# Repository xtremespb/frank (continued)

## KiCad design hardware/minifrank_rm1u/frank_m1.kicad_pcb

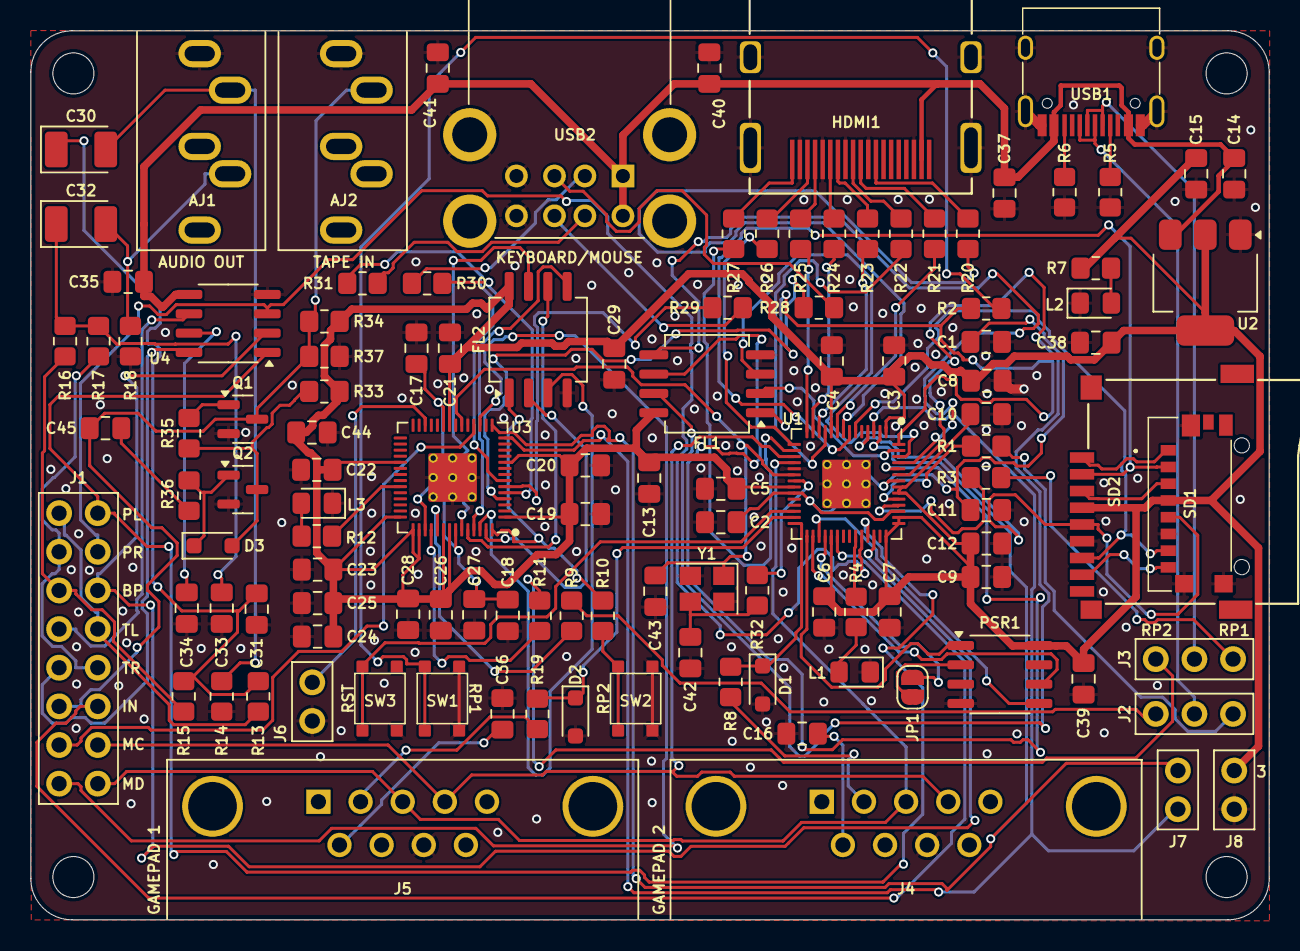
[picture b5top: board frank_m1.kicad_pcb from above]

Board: 2 copper layers, 81.4 x 58.4 mm, 121 parts (0 on the bottom side), 107 nets.

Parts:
AJ1, AJ2: SJ1-353XNG; Jack (3.5mm)
C1, C2, C3, C4, C5, C6, C7, C8, C9, C10, C13, C16, C17, C18, C19, C20, C21, C22, C23, C24, C25, C26, C29, C36, C37, C38, C39, C44, C45: 100n; Capacitor (0805)
C11, C12, C27, C28, C34: 1u; Capacitor (0805)
C14, C15, C40, C41: 10u; Capacitor (0805)
C30, C32: 10u; Capacitor (3528, tantalum, polar)
C31, C33: 10n; Capacitor (0805)
C35: 47u; Capacitor (0805)
C42, C43: 15p; Capacitor (0805)
D1, D2: 3V3; Diode (SOD-323)
D3: 1N4148; Diode (SOD-323)
FL1, FL2: W25Q128JVSIQ; SOIC-8
H1, H2, H3, H4: MountingHole; MountingHole_2.7mm
HDMI1: DC3RX19JA2; HDMI (female)
J1: Main Jumpers; Pin Header (2x08)
J2: USB DP Jumper; Pin Header (1x03)
J3: USB DM Jumper; Pin Header (1x03)
J4, J5: Gamepad; D-SUB (9 pin, male, top mount)
J6: RP2 Reset; Pin Header (1x02)
J7: UART; Pin Header (1x02)
J8: +3.3V; Pin Header (1x02)
JP1: Jumper PSRAM (2.54); Jumper (solder)
L1, L3: Blue; LED (0805)
L2: Green; LED (0805)
PSR1: ESP-PSRAM32; SO-8
Q1, Q2: BC850; SOT-23
R1, R3, R9, R11: 27R; Resistor (0805)
R2, R4, R7, R8, R10, R12, R13, R17, R19, R32, R34: 1K; Resistor (0805)
R5, R6: 5.1K; Resistor (0805)
R14, R18: 330R; Resistor (0805)
R15, R16: 2K; Resistor (0805)
R20, R21, R22, R23, R24, R25, R26, R27: 270R; Resistor (0805)
R28, R29, R30, R31: 22R; Resistor (0805)
R33, R35, R36: 10K; Resistor (0805)
R37: 100R; Resistor (0805)
SD1: 47571-0001; MicroSD (SMD, short)
SD2: 104031-0811; MicroSD (SMD, long)
SW1, SW2: KLS7-TS3302; Button (SMD, 3x3mm, 1-1)
SW3: KLS7-TS3302; Button (SMD, 3x3mm)
U1, U3: RP2040; QFN 56
U2: NCP1117 3.3; SOT-223
U4: TDA1387T; SO-8
USB1: USB4215; USB Type C
USB2: SS-52100-004; USB Type A (stacked)
Y1: 12 MHz; Crystal (3225)

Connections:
+3V3: C3.1, C4.1, C5.1, C6.1, C7.1, C8.1, C9.1, C10.1, C12.1, C13.1, C15.1, C19.1, C20.1, C21.1, C22.1, C23.1, C24.1, C25.1, C26.1, C28.1, C29.1, C38.2, C39.1, C44.1, FL1.8 (VCC), FL2.8 (VCC), J8.1, PSR1.8 (VCC), R7.2, R33.1, R34.1, SD1.P4 (VDD), SD2.4 (VDD), U1.1 (IOVDD), U1.10 (IOVDD), U1.22 (IOVDD), U1.33 (IOVDD), U1.42 (IOVDD), U1.43 (ADC_AVDD), U1.44 (VREG_IN), U1.48 (USB_VDD), U1.49 (IOVDD), U2.2 (VO), U3.1 (IOVDD), U3.10 (IOVDD), U3.22 (IOVDD), U3.33 (IOVDD), U3.42 (IOVDD), U3.43 (ADC_AVDD), U3.44 (VREG_IN), U3.48 (USB_VDD), U3.49 (IOVDD)
/A_OUTB: J1.5, R15.2, R16.2
/A_OUTL: J1.1, J1.8, R13.2
/A_OUTR: J1.3, J1.10, R17.2
/A_TDAL: J1.7, U4.6 (A_LEFT)
/A_TDAR: J1.9, U4.8 (A_RIGHT)
/Audio Out/L: AJ1.T, C30.2, R14.1
/Audio Out/R: AJ1.R, C32.2, R18.1
/GPIO0: J7.1, U1.2 (GPIO0), U3.15 (GPIO12)
/GPIO1: J7.2, U1.3 (GPIO1), U3.14 (GPIO11)
/GPIO2: SD1.P5 (CLK), SD2.5 (CLK), U1.4 (GPIO2)
/GPIO3: SD1.P3 (CMD), SD2.3 (CMD)
/GPIO4: SD1.P7 (DAT0), SD2.7 (DAT0), U1.6 (GPIO4)
/GPIO5: SD1.P2 (CD/DAT3), SD2.2 (DAT3/CD), U1.7 (GPIO5)
/GPIO6: R20.2, U1.8 (GPIO6)
/GPIO7: R21.2, U1.9 (GPIO7)
/GPIO8: R22.2, U1.11 (GPIO8)
/GPIO9: R23.2, U1.12 (GPIO9)
/GPIO10: R24.2, U1.13 (GPIO10)
/GPIO11: R25.2, U1.14 (GPIO11)
/GPIO12: R26.2, U1.15 (GPIO12)
/GPIO13: R27.2, U1.16 (GPIO13)
/GPIO14: J1.14, J4.4, J5.4, U1.17 (GPIO14)
/GPIO15: J1.16, J4.3, J5.3, U1.18 (GPIO15)
/GPIO16: D2.1 (K), R19.1, U1.27 (GPIO16)
/GPIO17: D1.1 (K), R8.1, U1.28 (GPIO17)
/GPIO18: PSR1.1 (~CE), U1.29 (GPIO18)
/GPIO19: PSR1.6 (SCLK), U1.30 (GPIO19)
/GPIO20: PSR1.5 (SI/SIO), U1.31 (GPIO20)
/GPIO21: JP1.2 (B), U1.32 (GPIO21)
/GPIO22: J1.12, U1.34 (GPIO22)
/GPIO26: J1.4, U1.38 (GPIO26_ADC0), U4.3 (DATA)
/GPIO27: J1.2, U1.39 (GPIO27_ADC1), U4.1 (SCLK)
/GPIO28: J1.6, U1.40 (GPIO28_ADC2), U4.2 (LRCK)
/Gamepad 1/+5V: C36.1, J5.6
/Gamepad 1/J1_DATA: J5.2, R19.2
/Gamepad 2/+5V: C16.1, J4.6
/Gamepad 2/J1_DATA: J4.2, R8.2
/LOAD_IN: AJ2.T, C45.1, J1.11, Q1.3 (C), R34.2, R37.1
/MS_CLK: J1.13, U3.18 (GPIO15)
/MS_DATA: J1.15, U3.17 (GPIO14)
/Micro SD/DAT1: SD1.P8 (DAT1), SD2.8 (DAT1)
/Micro SD/DAT2: SD1.P1 (DAT2), SD2.1 (DAT2)
/P_DM: J3.2, USB1.5 (DN2), USB1.7 (DN1)
/P_DP: J2.2, USB1.6 (DP1), USB1.8 (DP2)
/RP1/GPIO25: R4.2, U1.37 (GPIO25)
/RP1/QSPI_SCLK: FL1.6 (CLK), U1.52 (QSPI_SCLK)
/RP1/QSPI_SD0: FL1.5 (DI(IO0)), U1.53 (QSPI_SD0)
/RP1/QSPI_SD1: FL1.2 (DO(IO1)), U1.55 (QSPI_SD1)
/RP1/QSPI_SD2: FL1.3 (IO2), U1.54 (QSPI_SD2)
/RP1/QSPI_SD3: FL1.7 (IO3), U1.51 (QSPI_SD3)
/RP1/QSPI_SS: FL1.1 (~CS), R2.1, U1.56 (QSPI_SS)
/RP1/~USB_BOOT: R2.2, SW1.2
/RP1_DM: J3.1, R3.1
/RP1_DP: J2.1, R1.1
/RP2/GPIO25: R12.2, U3.37 (GPIO25)
/RP2/QSPI_SCLK: FL2.6 (CLK), U3.52 (QSPI_SCLK)
/RP2/QSPI_SD0: FL2.5 (DI(IO0)), U3.53 (QSPI_SD0)
/RP2/QSPI_SD1: FL2.2 (DO(IO1)), U3.55 (QSPI_SD1)
/RP2/QSPI_SD2: FL2.3 (IO2), U3.54 (QSPI_SD2)
/RP2/QSPI_SD3: FL2.7 (IO3), U3.51 (QSPI_SD3)
/RP2/QSPI_SS: FL2.1 (~CS), R10.1, U3.56 (QSPI_SS)
/RP2/~USB_BOOT: R10.2, SW2.2
/RP2_DM: J3.3, R11.1
/RP2_DP: J2.3, R9.1
/RP2_RUN: J6.1, U3.26 (RUN)
/RUN: SW3.3, SW3.4, U1.26 (RUN)
/US_D1M: R30.1, U3.5 (GPIO3)
/US_D1P: R28.1, U3.4 (GPIO2)
/US_D2M: R31.1, U3.7 (GPIO5)
/US_D2P: R29.1, U3.6 (GPIO4)
/XIN: C43.1, U1.20 (XIN), U3.20 (XIN), Y1.1
/XOUT: R32.1, U1.21 (XOUT)
GND: AJ1.S, AJ2.S, C1.2, C2.2, C3.2, C4.2, C5.2, C6.2, C7.2, C8.2, C9.2, C10.2, C11.2, C12.2, C13.2, C14.2, C15.2, C16.2, C17.2, C18.2, C19.2, C20.2, C21.2, C22.2, C23.2, C24.2, C25.2, C26.2, C27.2, C28.2, C29.2, C31.2, C33.2, C34.2, C35.1, C36.2, C37.2, C38.1, C39.2, C40.2, C41.2, C42.2, C43.2, C44.2, D1.2 (A), D2.2 (A), FL1.4 (GND), FL2.4 (GND), HDMI1.2 (G_D2), HDMI1.5 (G_D1), HDMI1.8 (G_D0), HDMI1.11 (G_CLK), HDMI1.17 (G_DDC/CEC), HDMI1.20 (SHIELD1), HDMI1.21 (SHIELD2), HDMI1.22 (SHIELD3), HDMI1.23 (SHIELD4), J4.8, J5.8, J6.2, J8.2, L1.1 (K), L2.1 (K), L3.1 (K), PSR1.4 (VSS), Q1.2 (E), Q2.2 (E), R5.1, R6.1, R14.2, R18.2, R37.2, SD1.G1 (GND_1), SD1.G2 (GND_2), SD1.G3 (GND_3), SD1.P6 (VSS), SD2.6 (VSS), SW1.1, SW2.1, SW3.1, SW3.2, U1.19 (TESTEN), U1.57 (GND), U2.1 (GND), U3.19 (TESTEN), U3.57 (GND), U4.4 (AGND), USB1.1 (GND), USB1.12 (GND), USB1.13 (SHIELD), USB2.4 (GND1), USB2.8 (GND2), USB2.9 (Shield), Y1.2, Y1.4
unnamed: C30.1, C31.1, R13.1, R15.1
unnamed: C32.1, C33.1, R16.1, R17.1
unnamed: C42.1, R32.2, Y1.3
unnamed: C45.2, R36.1
unnamed: D3.2 (A), Q2.3 (C), R33.2, R35.1
unnamed: D3.1 (K), Q2.1 (B), R36.2
unnamed: HDMI1.12 (CLKN), R20.1
unnamed: HDMI1.10 (CLKP), R21.1
unnamed: HDMI1.9 (D0N), R22.1
unnamed: HDMI1.7 (D0P), R23.1
unnamed: HDMI1.6 (D1N), R24.1
unnamed: HDMI1.4 (D1P), R25.1
unnamed: HDMI1.3 (D2N), R26.1
unnamed: HDMI1.1 (D2P), R27.1
unnamed: JP1.1 (A), PSR1.2 (SO/SIO)
unnamed: L1.2 (A), R4.1
unnamed: L2.2 (A), R7.1
unnamed: L3.2 (A), R12.1
unnamed: Q1.1 (B), R35.2
unnamed: R3.2, U1.46 (USB_DM)
unnamed: R1.2, U1.47 (USB_DP)
unnamed: C1.1, C2.1, C11.1, U1.23 (DVDD), U1.45 (VREG_VOUT), U1.50 (DVDD)
unnamed: R11.2, U3.46 (USB_DM)
unnamed: R9.2, U3.47 (USB_DP)
unnamed: C17.1, C18.1, C27.1, U3.23 (DVDD), U3.45 (VREG_VOUT), U3.50 (DVDD)
unnamed: C34.1, U4.7 (FLT)
unnamed: R5.2, USB1.4 (CC1)
unnamed: R6.2, USB1.10 (CC2)
unnamed: R28.2, USB2.3 (D1+)
unnamed: R30.2, USB2.2 (D1-)
unnamed: R29.2, USB2.7 (D2+)
unnamed: R31.2, USB2.6 (D2-)
VBUS: C14.1, C35.2, C37.1, C40.1, C41.1, HDMI1.18 (+5V), U2.3 (VI), U4.5 (VA), USB1.2 (VBUS), USB1.11 (VBUS), USB2.1 (VBUS1), USB2.5 (VBUS2)

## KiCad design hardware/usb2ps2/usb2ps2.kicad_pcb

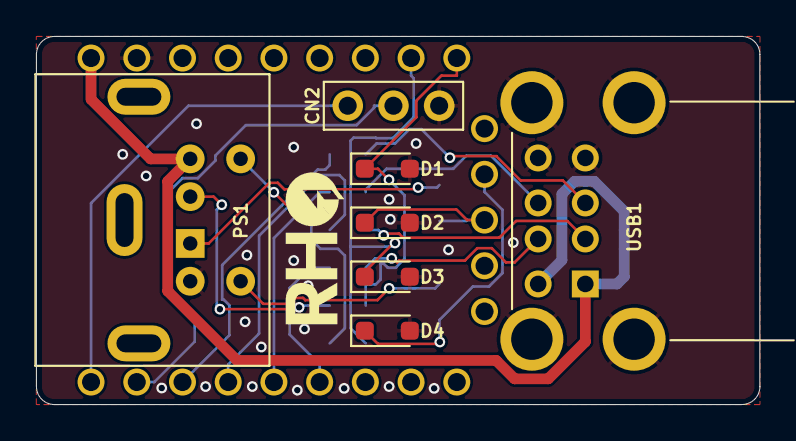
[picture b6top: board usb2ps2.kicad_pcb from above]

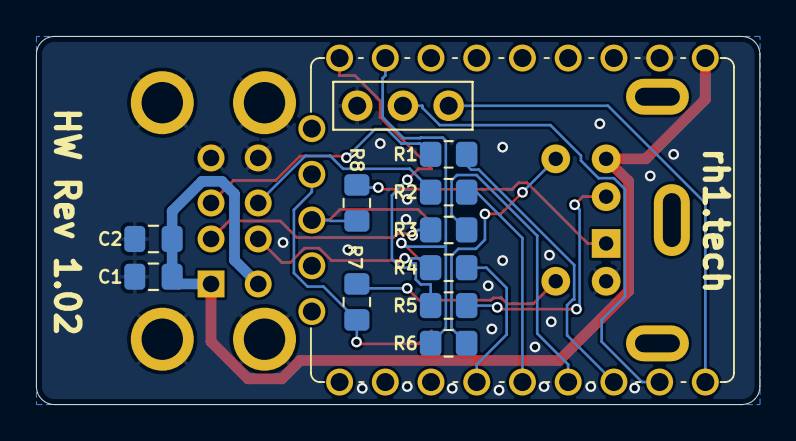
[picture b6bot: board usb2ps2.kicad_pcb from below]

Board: 2 copper layers, 40.2 x 20.4 mm, 18 parts (11 on the bottom side), 20 nets.

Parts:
C1, C2: 10u; Capacitor (0805)
CN2: UART; Pin Header (1x03)
D1, D2, D3, D4: 3V3; Diode (SOD-323)
PS1: PS/2; MiniDIN (6 Pin, female)
R1, R2, R3, R4: 22R; Resistor (0805)
R5, R6, R7, R8: 100R; Resistor (0805)
RP1: RP 2040 Zero; Raspberry Pi Zero (Outer pins)
USB1: USB_A_Stacked; USB Type A (stacked)

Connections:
/GPIO0: CN2.1, RP1.1 (0)
/GPIO1: CN2.2, RP1.2 (1)
/GPIO2: R1.1, RP1.3 (2)
/GPIO3: R3.1, RP1.4 (3)
/GPIO4: R2.1, RP1.5 (4)
/GPIO5: R4.1, RP1.6 (5)
/GPIO11: D2.1 (K), R8.2, RP1.12 (11)
/GPIO12: D4.1 (K), R7.2, RP1.13 (12)
/GPIO14: D1.1 (K), R5.2, RP1.15 (14)
/GPIO15: D3.1 (K), R6.2, RP1.16 (15)
/PS2 with Diodes/KB_CLK: PS1.5, R7.1
/PS2 with Diodes/KB_DATA: PS1.1, R8.1
/PS2 with Diodes/MS_CLK: PS1.6, R6.1
/PS2 with Diodes/MS_DATA: PS1.2, R5.1
GND: C1.2, C2.2, CN2.3, D1.2 (A), D2.2 (A), D3.2 (A), D4.2 (A), PS1.3, RP1.22 (GND), USB1.4 (GND1), USB1.8 (GND2), USB1.9 (Shield)
unnamed: R1.2, USB1.3 (D1+)
unnamed: R3.2, USB1.2 (D1-)
unnamed: R2.2, USB1.7 (D2+)
unnamed: R4.2, USB1.6 (D2-)
VBUS: C1.1, C2.1, PS1.4, RP1.23 (5V), USB1.1 (VBUS1), USB1.5 (VBUS2)

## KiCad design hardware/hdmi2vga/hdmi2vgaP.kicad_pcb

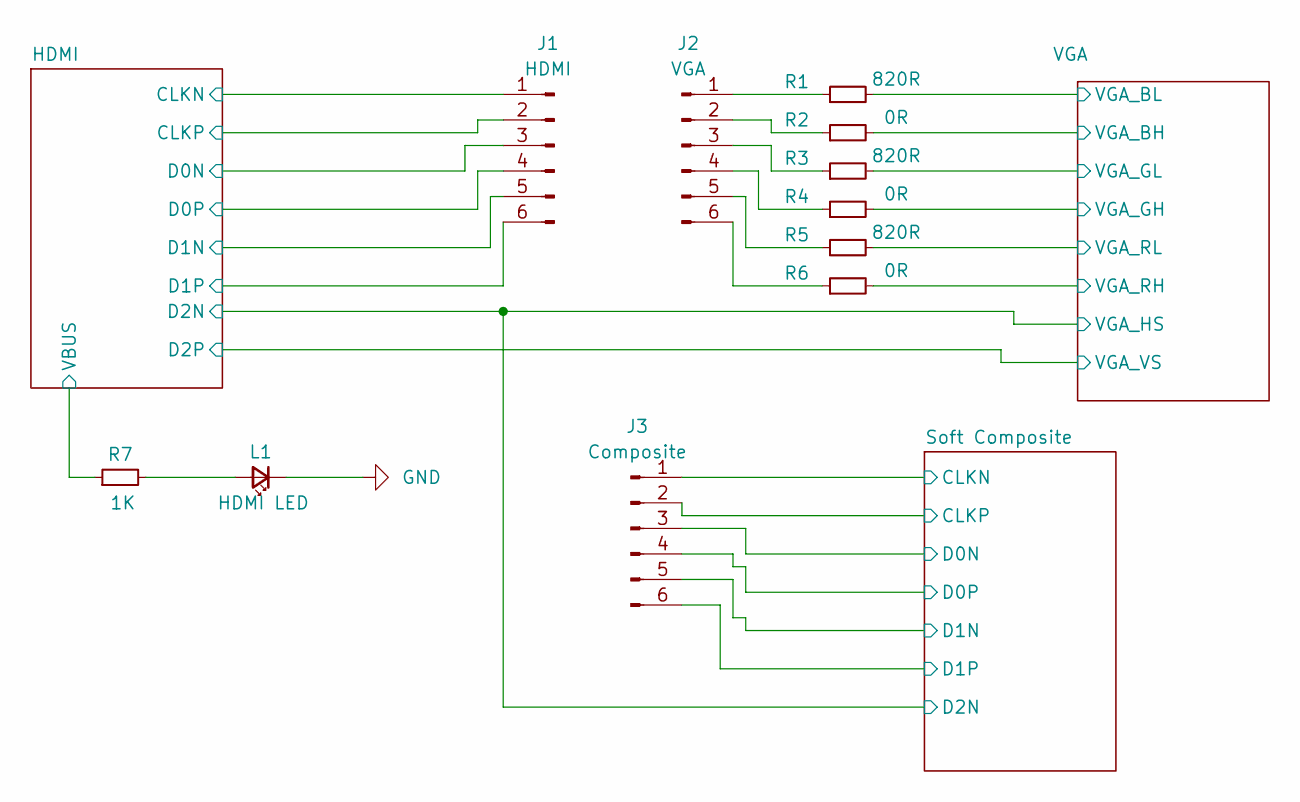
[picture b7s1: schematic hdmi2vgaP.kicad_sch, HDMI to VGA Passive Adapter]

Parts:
J1: HDMI; Medved_Pinheader_6P
J2: VGA; Medved_Pinheader_6P
J3: Composite; Medved_Pinheader_6P
L1: HDMI LED; LED_0805_2012Metric_Pad1.15x1.40mm_HandSolder
R1, R3, R5: 820R; R_0805_2012Metric_Pad1.20x1.40mm_HandSolder
R2, R4, R6: 0R; R_0805_2012Metric_Pad1.20x1.40mm_HandSolder
R7: 1K; R_0805_2012Metric_Pad1.20x1.40mm_HandSolder

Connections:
/HDMI/CLKN: J1.1; also elsewhere on the board
/HDMI/CLKP: J1.2; also elsewhere on the board
/HDMI/D0N: J1.3; also elsewhere on the board
/HDMI/D0P: J1.4; also elsewhere on the board
/HDMI/D1N: J1.5; also elsewhere on the board
/HDMI/D1P: J1.6; also elsewhere on the board
/HDMI/VBUS: R7.1; also elsewhere on the board
/Soft Composite/CLKN: J3.1; also elsewhere on the board
/Soft Composite/CLKP: J3.2; also elsewhere on the board
/Soft Composite/D0N: J3.3; also elsewhere on the board
/Soft Composite/D0P: J3.4; also elsewhere on the board
/Soft Composite/D1N: J3.5; also elsewhere on the board
/Soft Composite/D1P: J3.6; also elsewhere on the board
/VGA/VGA_BH: R1.2, R2.2; also elsewhere on the board
/VGA/VGA_GH: R3.2, R4.2; also elsewhere on the board
/VGA/VGA_RH: R5.2, R6.2; also elsewhere on the board
GND: L1.1 (K); also elsewhere on the board
unnamed: J2.1, R1.1
unnamed: J2.2, R2.1
unnamed: J2.3, R3.1
unnamed: J2.4, R4.1
unnamed: J2.5, R5.1
unnamed: J2.6, R6.1
unnamed: L1.2 (A), R7.2

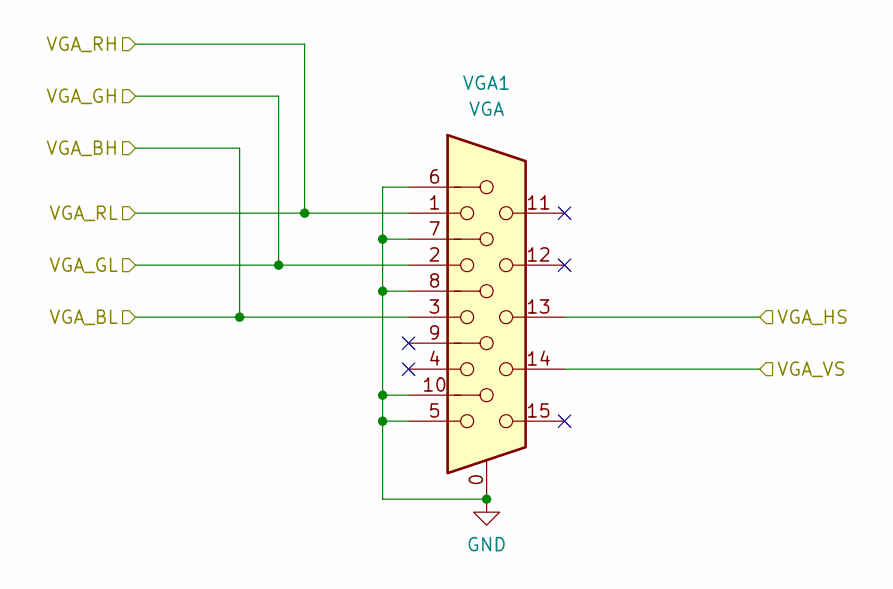
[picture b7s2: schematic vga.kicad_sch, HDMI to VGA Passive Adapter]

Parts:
VGA1: VGA; D-SUB (15 pin, female)

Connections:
/HDMI/D2N: VGA1.13; also elsewhere on the board
/HDMI/D2P: VGA1.14; also elsewhere on the board
/VGA/VGA_BH: VGA1.3; also elsewhere on the board
/VGA/VGA_GH: VGA1.2; also elsewhere on the board
/VGA/VGA_RH: VGA1.1; also elsewhere on the board
GND: VGA1.0, VGA1.5, VGA1.6, VGA1.7, VGA1.8, VGA1.10; also elsewhere on the board

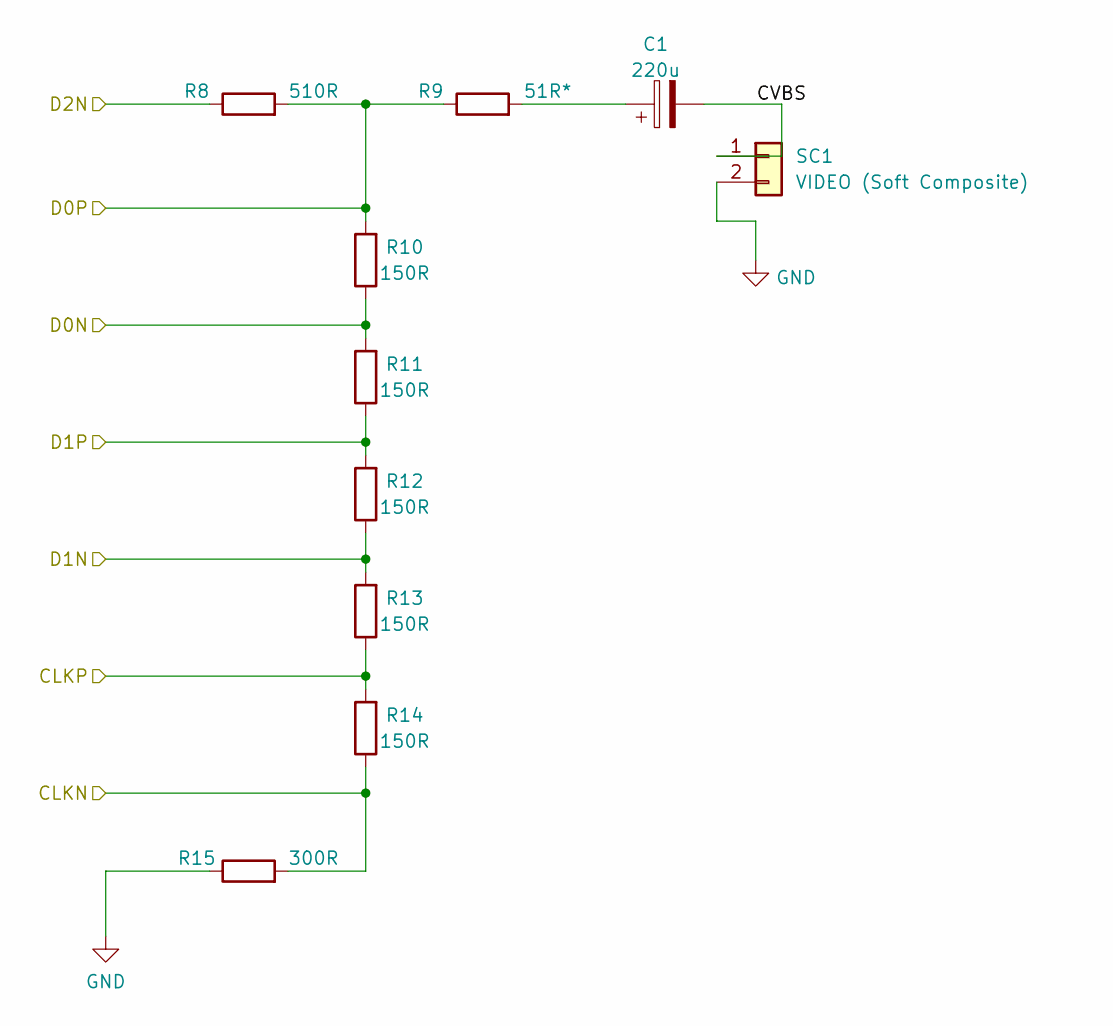
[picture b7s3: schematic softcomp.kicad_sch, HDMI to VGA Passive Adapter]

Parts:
C1: 220u; Capacitor (3528, tantalum, polar)
R8: 510R; Resistor (0805)
R9: 51R*; Resistor (0805)
R10, R11, R12, R13, R14: 150R; Resistor (0805)
R15: 300R; Resistor (0805)
SC1: VIDEO (Soft Composite); RCA

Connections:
/HDMI/D2N: R8.1; also elsewhere on the board
/Soft Composite/CLKN: R14.1, R15.2; also elsewhere on the board
/Soft Composite/CLKP: R13.1, R14.2; also elsewhere on the board
/Soft Composite/CVBS: C1.2, SC1.1
/Soft Composite/D0N: R10.1, R11.2; also elsewhere on the board
/Soft Composite/D0P: R8.2, R9.1, R10.2; also elsewhere on the board
/Soft Composite/D1N: R12.1, R13.2; also elsewhere on the board
/Soft Composite/D1P: R11.1, R12.2; also elsewhere on the board
GND: R15.1, SC1.2; also elsewhere on the board
unnamed: C1.1, R9.2

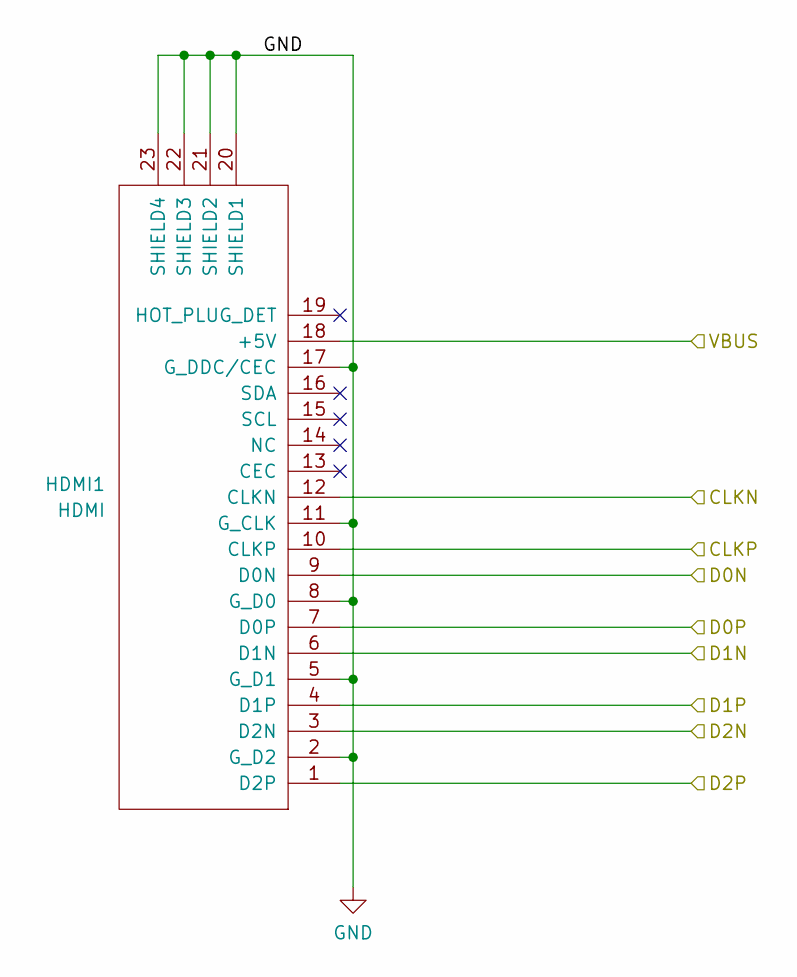
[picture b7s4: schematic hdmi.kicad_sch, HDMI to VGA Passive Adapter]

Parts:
HDMI1: HDMI; HDMI (male)

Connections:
/HDMI/CLKN: HDMI1.12 (CLKN); also elsewhere on the board
/HDMI/CLKP: HDMI1.10 (CLKP); also elsewhere on the board
/HDMI/D0N: HDMI1.9 (D0N); also elsewhere on the board
/HDMI/D0P: HDMI1.7 (D0P); also elsewhere on the board
/HDMI/D1N: HDMI1.6 (D1N); also elsewhere on the board
/HDMI/D1P: HDMI1.4 (D1P); also elsewhere on the board
/HDMI/D2N: HDMI1.3 (D2N); also elsewhere on the board
/HDMI/D2P: HDMI1.1 (D2P); also elsewhere on the board
/HDMI/VBUS: HDMI1.18 (+5V); also elsewhere on the board
GND: HDMI1.2 (G_D2), HDMI1.5 (G_D1), HDMI1.8 (G_D0), HDMI1.11 (G_CLK), HDMI1.17 (G_DDC/CEC), HDMI1.20 (SHIELD1), HDMI1.21 (SHIELD2), HDMI1.22 (SHIELD3), HDMI1.23 (SHIELD4); also elsewhere on the board

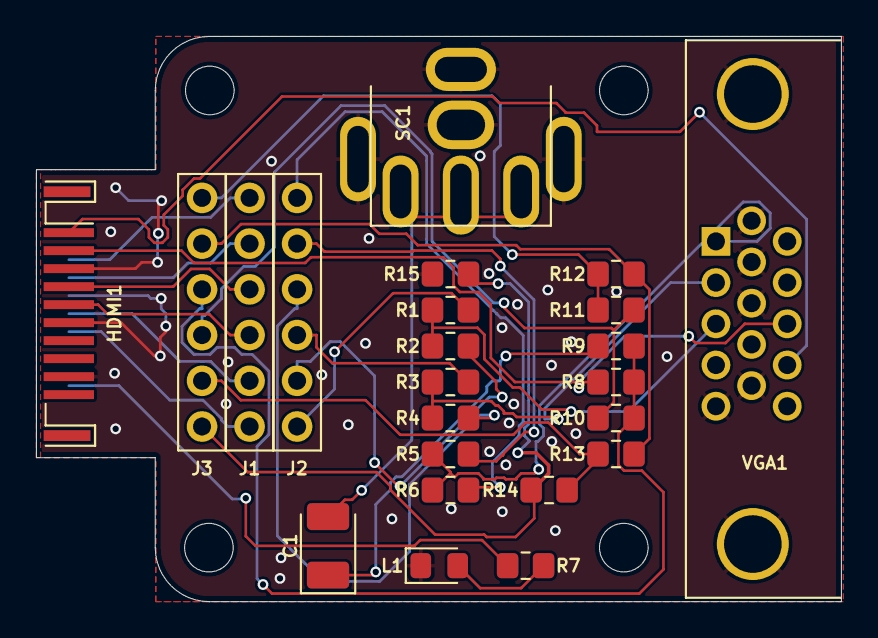
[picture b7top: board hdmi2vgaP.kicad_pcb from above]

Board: 2 copper layers, 44.7 x 31.4 mm, 27 parts (0 on the bottom side), 28 nets.

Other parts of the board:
H1, H2, H3, H4: MountingHole; Mounting Hole (2.7mm)

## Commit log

2024-08-20 Fixes
2024-08-21 3D Models added
2024-08-21 Scheme & PCB updates
2024-08-21 AV Video output added
2024-08-22 Added HDMI port
2024-08-23 Some minor changes
2024-08-23 New HW revision
2024-08-24 Work in progress
2024-08-26 Revision updates
2024-08-26 HW Rev 1.0 Preview
2024-08-27 HW REV 1.0
2024-08-27 HW 1.01
2024-08-27 HW Rev 1.02
2024-08-27 HW Rev. 1.04
2024-09-04 Minor updates
2024-09-04 HW Version 1.5
2024-09-04 HW 1.6 WIP
2024-09-05 HW Rev. 1.6 WIP
2024-09-08 Changed MAX232 to level shifter
2024-09-08 HW Version 1.8
2024-09-09 HW Revision 1.8
2024-09-09 Removed/archived unused files
2024-09-09 Added schematics
2024-09-10 HW Rev 1.08
2024-10-02 HW Rev 1.09
2024-10-04 MAX232-related changes
2024-10-04 HW Rev 1.10
2024-10-23 HW Rev 1.12
2024-11-22 Minor fixes
2025-01-04 README added
2025-01-05 German README added
2025-01-12 Cleanup
2025-01-12 Gerbes added
2025-01-12 Master branch cleanup
2025-01-14 HW Rev 2.0
2025-01-31 HW Rev 1.0 work-in-progress
2025-01-31 Frank M2 HW Rev 1.0
2025-02-02 Fixed audio pins
2025-02-02 HW Rev 1.01
2025-02-02 HW Rev 1.2
2025-02-02 HW Rev 2.01
2025-02-02 Wrong filename fixed
2025-02-03 FRANK M1 work-in-progress
2025-02-03 Work-in-progress
2025-02-04 FRANK M1 HW Rev 1.00
2025-02-05 FRANK M2U WIP
2025-02-06 FRANK M2U HW Rev 1.00
2025-02-18 FRANK WIP
2025-02-18 Names changed
2025-02-19 Added archive directory
2025-02-19 FRANK M1 & M2 HW Revisions
2025-02-19 USB2PS2 Zero HW REV 1.1
2025-02-21 Moved RM2(x) versions to archive
2025-02-22 FRANK RM2 WIP
2025-02-23 MiniFRANK RM2 HW 1.03
2025-02-24 Case for 1.01 added
2025-03-03 Versa renamed to Protea
2025-03-03 Protea HW Rev 2.02
2025-03-03 HW Rev 1.14
2025-03-03 HW Rev 1.02 (M2)
2025-03-03 Protea case added
2025-03-03 HDMI2VGA HW 2.01
2025-03-04 Structural updates
2025-03-04 RM1 HW 2.01
2025-03-04 Moving archives to ZIP files
2025-03-04 MiniFRANK updates
2025-03-04 Archived MiniFRANK RM2U
2025-03-05 RM1Z WIP
2025-03-05 FRANK RM1Z HW 1.00
2025-03-08 RM2E WIP
2025-03-08 Bugfixes
2025-03-12 MiniFRANK RM2F 1.00
2025-03-12 RM2 archived
2025-03-13 RM24 WIP
2025-03-14 MiniFRANK RM24 added
2025-03-14 Gerber updated
2025-03-14 RM24 minor fixes
